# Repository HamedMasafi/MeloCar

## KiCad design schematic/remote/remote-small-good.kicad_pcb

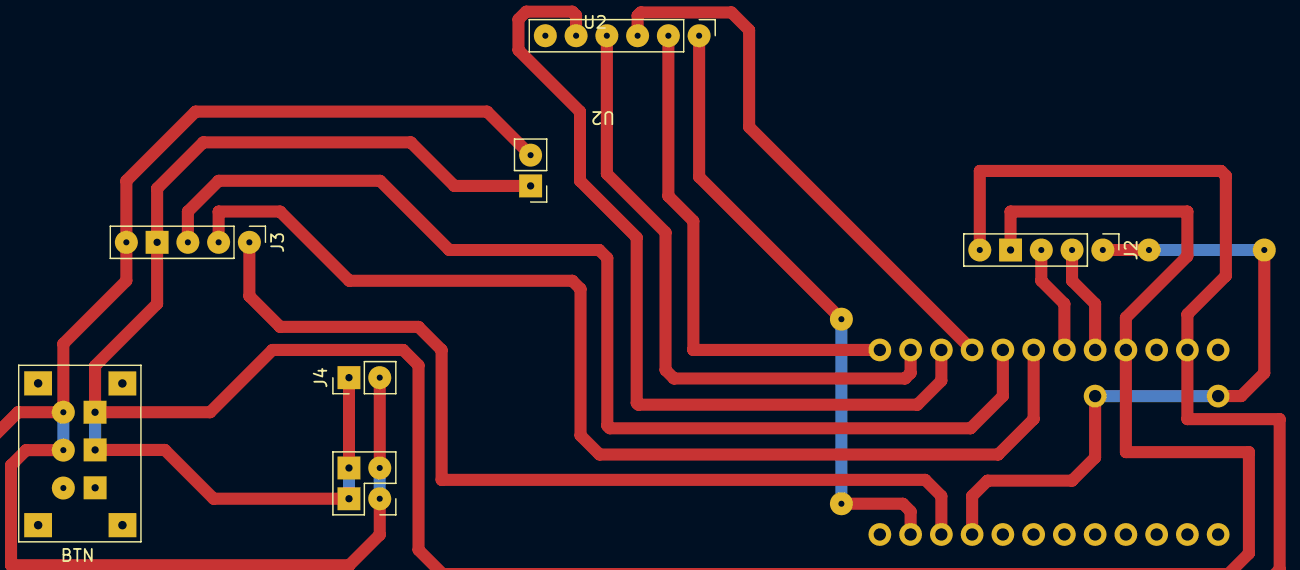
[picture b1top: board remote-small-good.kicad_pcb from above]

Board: 2 copper layers, 6 parts (1 on the bottom side), 13 nets.

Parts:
BTN: PushButton_6_pin
J2: Joystick_Left; PinHeader_1x05_P2.54mm_Vertical
J3: Joystick_Right; PinHeader_1x05_P2.54mm_Vertical
J4: Micro-Power-IN; PinHeader_1x02_P2.54mm_Vertical
U1: ARDUINO_PRO_MINI; MODULE_ARDUINO_PRO_MINI
U2: NRF24L01_Breakout; NRF24L01

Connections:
+5V: BTN.3, BTN.5, J2.4, J3.4, J4.1, U1.JP6_4 (VCC_1), U2.2 (VCC)
GND: BTN.4, BTN.6, J2.5, J3.5, J4.2, U1.JP6_2 (GND_1), U2.1 (GND)
unnamed: J2.1, U1.JP7_4 (D6)
unnamed: J2.2, U1.JP6_5 (A3)
unnamed: J2.3, U1.JP6_6 (A2)
unnamed: J3.1, U1.JP7_3 (D7)
unnamed: J3.2, U1.JP6_7 (A1)
unnamed: J3.3, U1.JP6_8 (A0)
unnamed: U1.JP6_9 (SCK), U2.5 (SCK)
unnamed: U1.JP6_10 (MISO), U2.7 (MISO)
unnamed: U1.JP6_11 (MOSI), U2.6 (MOSI)
unnamed: U1.JP6_12 (D10), U2.4 (~CSN)
unnamed: U1.JP7_2 (D8), U2.3 (CE)
